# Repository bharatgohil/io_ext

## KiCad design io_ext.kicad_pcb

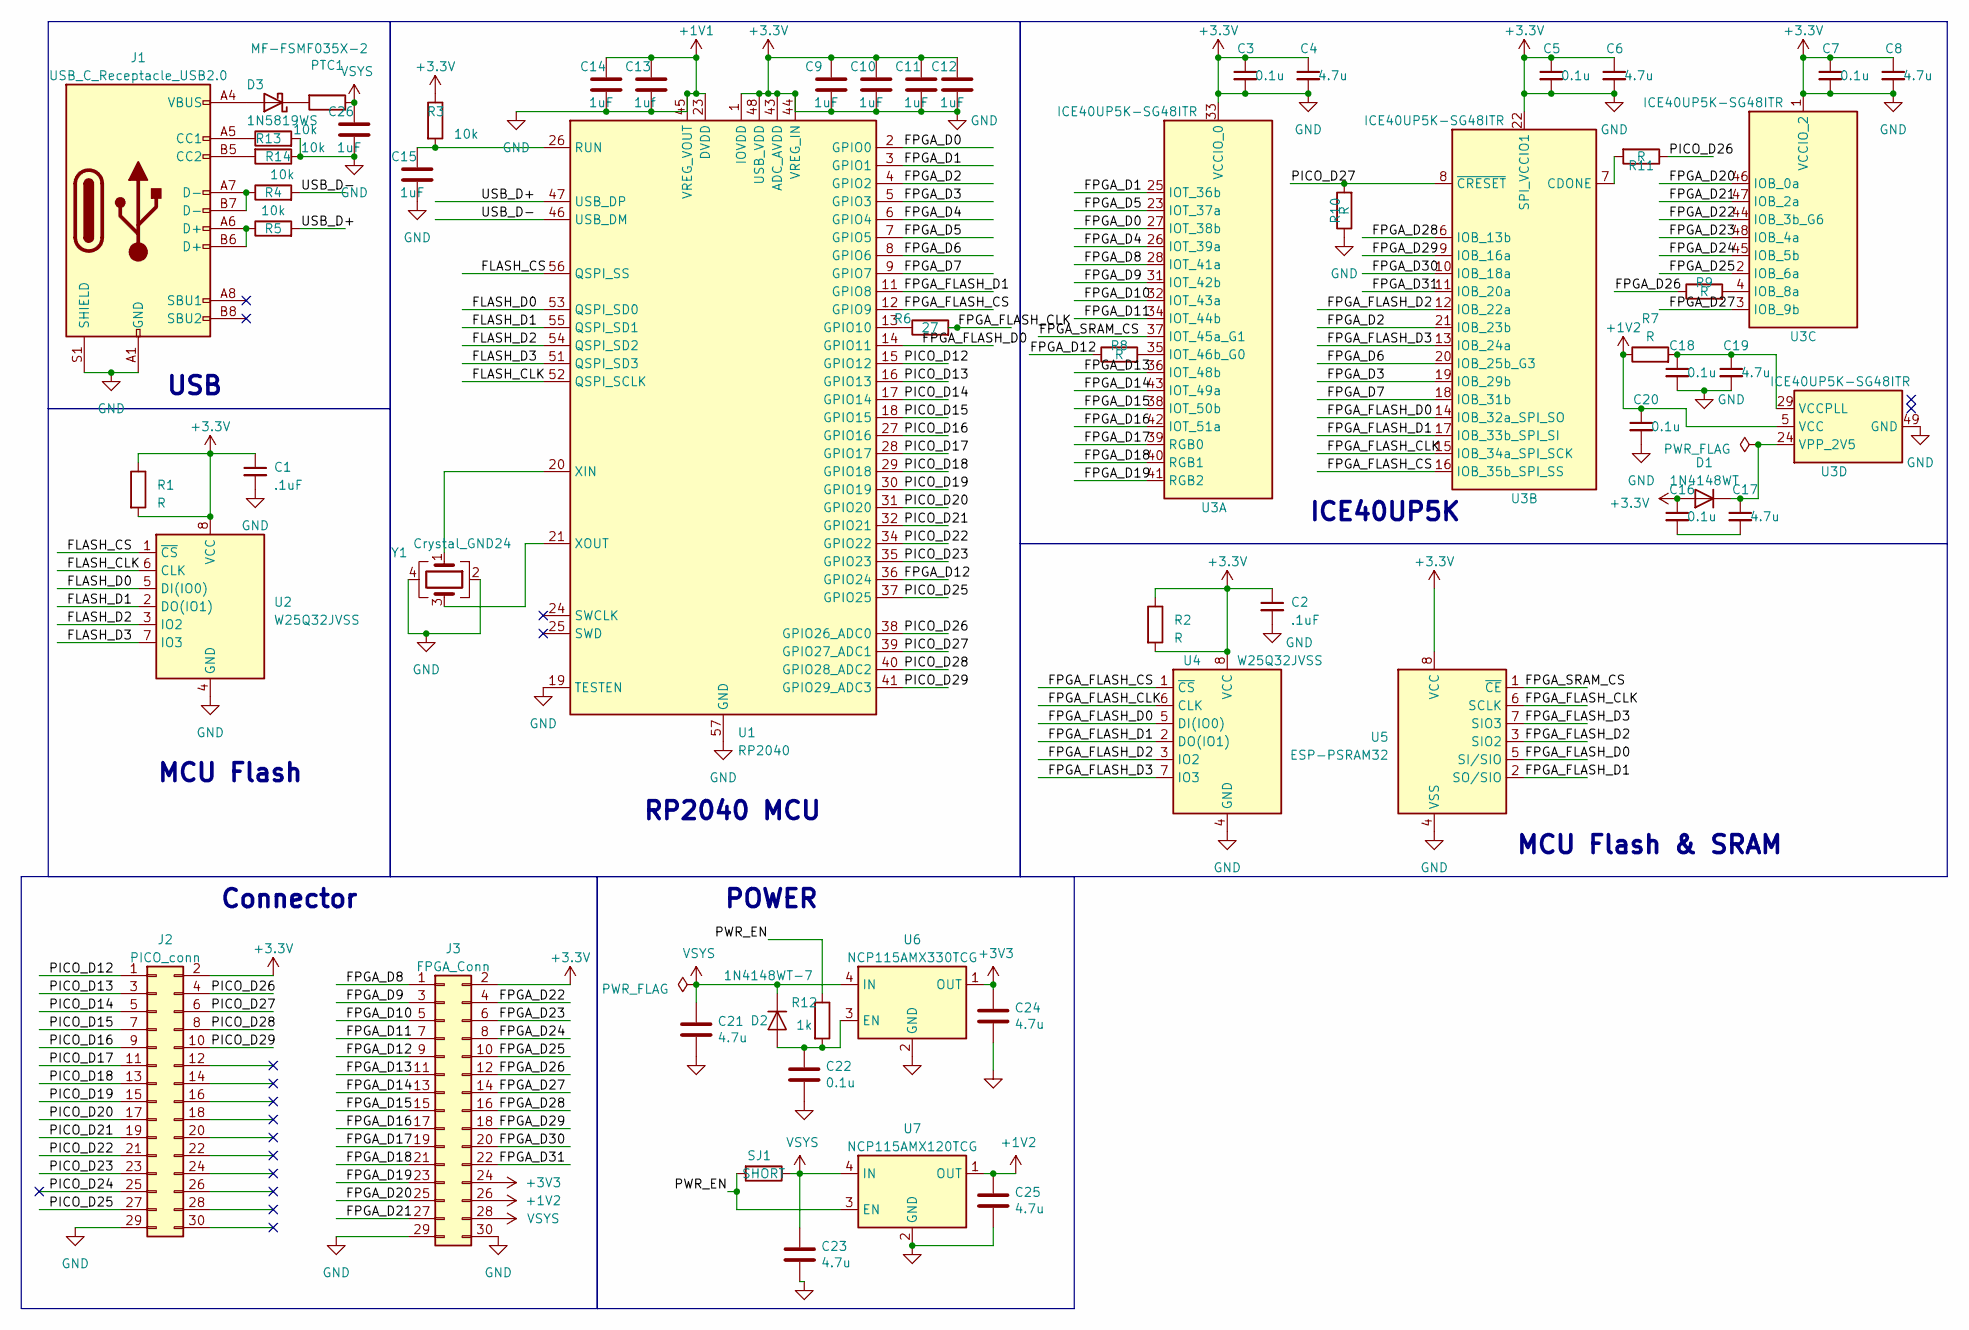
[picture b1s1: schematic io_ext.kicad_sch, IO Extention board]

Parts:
C1, C2: .1uF; C_0402_1005Metric
C3, C5, C7, C16, C18, C20: 0.1u; C_0402_1005Metric
C4, C6, C8, C17, C19: 4.7u; C_0402_1005Metric
C9, C10, C11, C12, C14, C15, C26: 1uF; C_0402_1005Metric
C13: 1uf; C_0402_1005Metric
C21, C23, C24, C25: 4.7u; C_0402_1005Metric; MPN GRM155R60J475ME87D
C22: 0.1u; C_0402_1005Metric; MPN GRM155R71C104KA88J
D1: 1N4148WT; D_SOD-523
D2: 1N4148WT-7; D_SOD-523; MPN 1N4148WT-7
D3: 1N5819WS; D_SOD-323; MPN 1N5819WS
J1: USB_C_Receptacle_USB2.0; USB_C_Plug_Molex_105444
J2: PICO_conn
J3: FPGA_Conn
PTC1: MF-FSMF035X-2; R_0603_1608Metric; MPN MF-FSMF035X-2
R1, R2, R7, R8, R9, R10, R11: R
R3, R4, R5, R13, R14: 10k
R6: 27
R12: 1k; R_0402_1005Metric; MPN RC0402FR-071KL
SJ1: SHORT; SolderJumper-2_P1.3mm_Bridged_RoundedPad1.0x1.5mm; MPN DNP
U1: RP2040; QFN-56-1EP_7x7mm_P0.4mm_EP3.2x3.2mm
U2, U4: W25Q32JVSS; SOIC-8_5.23x5.23mm_P1.27mm
U3: ICE40UP5K-SG48ITR; QFN-48-1EP_7x7mm_P0.5mm_EP5.6x5.6mm
U5: ESP-PSRAM32; SOIC-8_3.9x4.9mm_P1.27mm
U6: NCP115AMX330TCG; OnSemi_XDFN4-1EP_1.0x1.0mm_EP0.52x0.52mm; MPN NCP115AMX330TCG
U7: NCP115AMX120TCG; OnSemi_XDFN4-1EP_1.0x1.0mm_EP0.52x0.52mm; MPN NCP115AMX120TCG
Y1: Crystal_GND24

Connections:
+1V1: C1.1, C1.2, C2.1, C2.2, C3.1, C3.2, C4.1, C4.2, C5.1, C5.2, C6.1, C6.2, C7.1, C7.2, C8.1, C8.2, C9.1, C9.2, C10.1, C10.2, C11.1, C11.2, C12.1, C12.2, C13.1, C13.2, C14.1, C14.2, C15.2, C16.1, C18.2, C19.2, C20.2, C21.2, C22.2, C23.2, C24.2, C25.2, C26.2, D1.2 (A), J1.A1 (GND), J1.A12 (GND), J1.B1 (GND), J1.B12 (GND), J1.S1 (SHIELD), J2.2, J2.29, J3.2, J3.29, J3.30, R1.1, R1.2, R2.1, R2.2, R3.1, R10.1, R13.2, R14.1, U1.1 (IOVDD), U1.10 (IOVDD), U1.19 (TESTEN), U1.22 (IOVDD), U1.23 (DVDD), U1.33 (IOVDD), U1.42 (IOVDD), U1.43 (ADC_AVDD), U1.44 (VREG_IN), U1.45 (VREG_VOUT), U1.48 (USB_VDD), U1.49 (IOVDD), U1.50 (DVDD), U1.57 (GND), U2.4 (GND), U2.8 (VCC), U3.1 (VCCIO_2), U3.22 (SPI_VCCIO1), U3.33 (VCCIO_0), U3.49 (GND), U4.4 (GND), U4.8 (VCC), U5.4 (VSS), U5.8 (VCC), U6.2 (GND), U6.5 (GND), U7.2 (GND), U7.5 (GND), Y1.2, Y1.4
+1V2: C20.1, C25.1, J3.26, R7.1, U3.5 (VCC), U3.30 (VCC), U7.1 (OUT)
+3V3: C24.1, J3.24, U6.1 (OUT)
/FLASH_CLK: U1.52 (QSPI_SCLK), U2.6 (CLK)
/FLASH_CS: U1.56 (QSPI_SS), U2.1 (~CS)
/FLASH_D0: U1.53 (QSPI_SD0), U2.5 (DI(IO0))
/FLASH_D1: U1.55 (QSPI_SD1), U2.2 (DO(IO1))
/FLASH_D2: U1.54 (QSPI_SD2), U2.3 (IO2)
/FLASH_D3: U1.51 (QSPI_SD3), U2.7 (IO3)
/FPGA_D0: U1.2 (GPIO0), U3.27 (IOT_38b)
/FPGA_D1: U1.3 (GPIO1), U3.25 (IOT_36b)
/FPGA_D2: U1.4 (GPIO2), U3.21 (IOB_23b)
/FPGA_D3: U1.5 (GPIO3), U3.19 (IOB_29b)
/FPGA_D4: U1.6 (GPIO4), U3.26 (IOT_39a)
/FPGA_D5: U1.7 (GPIO5), U3.23 (IOT_37a)
/FPGA_D6: U1.8 (GPIO6), U3.20 (IOB_25b_G3)
/FPGA_D7: U1.9 (GPIO7), U3.18 (IOB_31b)
/FPGA_D8: J3.1, U3.28 (IOT_41a)
/FPGA_D9: J3.3, U3.31 (IOT_42b)
/FPGA_D10: J3.5, U3.32 (IOT_43a)
/FPGA_D11: J3.7, U3.34 (IOT_44b)
/FPGA_D12: J3.9, R8.1, U1.36 (GPIO24)
/FPGA_D13: J3.11, U3.36 (IOT_48b)
/FPGA_D14: J3.13, U3.43 (IOT_49a)
/FPGA_D15: J3.15, U3.38 (IOT_50b)
/FPGA_D16: J3.17, U3.42 (IOT_51a)
/FPGA_D17: J3.19, U3.39 (RGB0)
/FPGA_D18: J3.21, U3.40 (RGB1)
/FPGA_D19: J3.23, U3.41 (RGB2)
/FPGA_D20: J3.25, U3.46 (IOB_0a)
/FPGA_D21: J3.27, U3.47 (IOB_2a)
/FPGA_D22: J3.4, U3.44 (IOB_3b_G6)
/FPGA_D23: J3.6, U3.48 (IOB_4a)
/FPGA_D24: J3.8, U3.45 (IOB_5b)
/FPGA_D25: J3.10, U3.2 (IOB_6a)
/FPGA_D26: J3.12, R9.1
/FPGA_D27: J3.14, U3.3 (IOB_9b)
/FPGA_D28: J3.16, U3.6 (IOB_13b)
/FPGA_D29: J3.18, U3.9 (IOB_16a)
/FPGA_D30: J3.20, U3.10 (IOB_18a)
/FPGA_D31: J3.22, U3.11 (IOB_20a)
/FPGA_FLASH_CLK: R6.2, U3.15 (IOB_34a_SPI_SCK), U4.6 (CLK), U5.6 (SCLK)
/FPGA_FLASH_CS: U1.12 (GPIO9), U3.16 (IOB_35b_SPI_SS), U4.1 (~CS)
/FPGA_FLASH_D0: U1.14 (GPIO11), U3.14 (IOB_32a_SPI_SO), U4.5 (DI(IO0)), U5.5 (SI/SIO)
/FPGA_FLASH_D1: U1.11 (GPIO8), U3.17 (IOB_33b_SPI_SI), U4.2 (DO(IO1)), U5.2 (SO/SIO)
/FPGA_FLASH_D2: U3.12 (IOB_22a), U4.3 (IO2), U5.3 (SIO2)
/FPGA_FLASH_D3: U3.13 (IOB_24a), U4.7 (IO3), U5.7 (SIO3)
/FPGA_SRAM_CS: U3.37 (IOT_45a_G1), U5.1 (~CE)
/PICO_D12: J2.1, U1.15 (GPIO12)
/PICO_D13: J2.3, U1.16 (GPIO13)
/PICO_D14: J2.5, U1.17 (GPIO14)
/PICO_D15: J2.7, U1.18 (GPIO15)
/PICO_D16: J2.9, U1.27 (GPIO16)
/PICO_D17: J2.11, U1.28 (GPIO17)
/PICO_D18: J2.13, U1.29 (GPIO18)
/PICO_D19: J2.15, U1.30 (GPIO19)
/PICO_D20: J2.17, U1.31 (GPIO20)
/PICO_D21: J2.19, U1.32 (GPIO21)
/PICO_D22: J2.21, U1.34 (GPIO22)
/PICO_D23: J2.23, U1.35 (GPIO23)
/PICO_D24: J2.25
/PICO_D25: J2.27, U1.37 (GPIO25)
/PICO_D26: J2.4, R11.1, U1.38 (GPIO26_ADC0)
/PICO_D27: J2.6, R10.2, U1.39 (GPIO27_ADC1), U3.8 (~CRESET)
/PICO_D28: J2.8, U1.40 (GPIO28_ADC2)
/PICO_D29: J2.10, U1.41 (GPIO29_ADC3)
/PWR_EN: R12.1, SJ1.2, U7.3 (EN)
/USB_D+: R5.2, U1.47 (USB_DP)
/USB_D-: R4.2, U1.46 (USB_DM)
unnamed: C16.2, C17.2
unnamed: C17.1, D1.1 (K), U3.24 (VPP_2V5)
unnamed: C22.1, D2.2 (A), R12.2, U6.3 (EN)
unnamed: D3.2 (A), J1.A4 (VBUS), J1.A9 (VBUS), J1.B4 (VBUS), J1.B9 (VBUS)
unnamed: D3.1 (K), PTC1.2
unnamed: J1.A5 (CC1), R13.1
unnamed: J1.B5 (CC2), R14.2
unnamed: J1.A6 (D+), J1.B6 (D+), R5.1
unnamed: J1.A7 (D-), J1.B7 (D-), R4.1
unnamed: R6.1, U1.13 (GPIO10)
unnamed: C15.1, R3.2, U1.26 (RUN)
unnamed: U1.20 (XIN), Y1.1
unnamed: U1.21 (XOUT), Y1.3
unnamed: R8.2, U3.35 (IOT_46b_G0)
unnamed: R11.2, U3.7 (CDONE)
unnamed: R9.2, U3.4 (IOB_8a)
unnamed: C18.1, C19.1, R7.2, U3.29 (VCCPLL)
VBUS: C21.1, C23.1, C26.1, D2.1 (K), J3.28, PTC1.1, SJ1.1, U6.4 (IN), U7.4 (IN)

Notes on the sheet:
Connector
POWER
MCU Flash
ICE40UP5K
MCU Flash & SRAM
USB
RP2040 MCU

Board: 4 copper layers, 56 parts (0 on the bottom side), 86 nets, no tracks yet.

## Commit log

2023-07-24 Base commit
